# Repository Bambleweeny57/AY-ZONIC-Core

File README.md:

# 🔊AY-ZONIC-Core

AY-ZONIC-Core is a modular PSG interface designed for the ZX81, supporting both ZON-X and ZON-X-81 compatibility via simplified A4-only decode logic. Rev2.0 introduces gate economy, contributor-friendly schematic clarity, and expansion-ready I/O via AY-3-8912 Port A.

> **This project continues from [JonZON-X](https://github.com/Bambleweeny57/JonZON-X), which was closed at Rev1.4** after timing issues were discovered in demo playback. AY-ZONIC-Core retains the same A4-based decode logic but drops A5 and A6 simplifying the design to single PSG support and saving a gate.

## 🔧 Features

- **Dual-mode decode logic** via DIP switch:
  - **DIP OFF** → A4 pulled high → ZON-X-81 mode
  - **DIP ON** → A4 sourced from ZX81 Expansion Bus → ZON-X mode
- **AY-3-8912 PSG integration** with clean register selection and audio output
- **Series resistors** on data bus for signal protection
- **Pull-ups** from ZX81 Expansion Bus to PSG for stable logic levels
- **Port A expansion header** with +5V and GND for SD card and I/O experimentation
- **/RD decode support** for future peripheral interaction and PSG reads
### DIP Switch Logic — A4 Routing Modes

| DIP Switch | A4 Source             | Mode         | Description                                      |
|------------|-----------------------|--------------|--------------------------------------------------|
| OFF        | Pulled high (via pull-up) | ZON-X-81     | Forces A4 = 1 for simplified decode              |
| ON         | From ZX81 Expansion Bus  | ZON-X        | Enables dynamic A4 control from host             |

> This DIP-controlled logic allows seamless switching between ZON-X and ZON-X-81 compatibility without modifying the schematic.
> 
## 🧠 Decode Logic Overview

The schematic uses simplified A4-only address decoding, inherited from JonZON-X Rev1.4. By removing A5 and A6 from the decode path, Rev2.0 drops multi-PSG support in favor of gate economy and contributor clarity.

## 🖼️ Visual Decode Logic

### Decode Logic Explanation

The PSG is selected when:
- **A4 = 1** (via DIP or bus)
- **A7 = 1** (to avoid bus conflicts)
- **A2 = 1** (used internally by the PSG)
- **/IOREQ = 0** (active I/O cycle)
- **/WR and /RD** combinations determine the operation:
  - `/WR = 1`, `/RD = 1` → Write to register
  - `/WR = 0`, `/RD = 1` → Write to PSG
  - `/WR = 0`, `/RD = 0` → Read from PSG

> `/RD` is now decoded explicitly to support read operations from the PSG and future SD card and I/O interfaces.

### Reference — JonZON-X Rev1.4 Decode Matrix (A5/A6 omitted) for AY-ZONIC-Core

| A0–A4 | A2 | A7 | /IOREQ | /WR | /RD | BDIR | BC1 | Operation             |
|-------|----|----|--------|-----|-----|------|-----|------------------------|
| —     | 1  | 1  | 0      | 1   | 1   | 1    | 1   | Write to register      |
| —     | 1  | 1  | 0      | 0   | 1   | 0    | 1   | Write to PSG           |
| —     | 1  | 1  | 1      | 0   | 0   | 1    | 0   | Read from PSG          |
| —     | —  | —  | —      | —   | —   | 0    | 0   | Inactive               |

> Rev2.0 removes A5 and A6, streamlining the logic and focusing on single PSG support.

---

## 🔌 Expansion Header (Port A)

Port A of the AY-3-8912 exposes:
- **8 digital I/O lines** (AIO0–AIO7)
- **+5V** and **GND** for powering peripherals

This enables SD card interfacing, experimental I/O modules, and future expansion without modifying the core schematic.

### 🧵 AY-ZONIC-Core I/O Connector Pinout

| Pin | Signal | Description            |
|-----|--------|------------------------|
| 1   | 5V     | Power supply (5 volts) |
| 2   | A0     | Address line 0         |
| 3   | A1     | Address line 1         |
| 4   | A2     | Address line 2         |
| 5   | A3     | Address line 3         |
| 6   | A4     | Address line 4         |
| 7   | A5     | Address line 5         |
| 8   | A6     | Address line 6         |
| 9   | A7     | Address line 7         |
| 10  | GND    | Ground                 |

> This header is ideal for SD card experiments, LED arrays, or future playback logic modules. All signals are directly mapped from the AY-3-8912 Port A.

---

## 🗂️ Repository Structure

- `README.md` — This file
- `src/` — schematic and PCB design files (KiCad v9+)
- `pdf/ay-zonic-core.pdf` — Rev2.x schematic (KiCad source available from /src)
- `images/` — Decode logic diagram and overlays
- `fabfiles/` — Gerber and Exelon Drill fabrication files
- `docs/` — Contributor notes and onboarding diagrams (coming soon)

## 🧭 Contributor Notes

- Keep DIP switch logic annotated in overlays
- Label Port A lines clearly for expansion use
- Use series resistors and pull-ups as shown for safe bus interaction
- Future revisions may include playback logic or UI hooks — modularity is key

## 🛠️ Status

✅ Rev2.0 schematic complete  
🧪 Expansion header tested with SD interface  
📚 Documentation in progress

---

For questions, forks, or onboarding help, feel free to open an issue or start a discussion. Let the AY-3-8912 sing!

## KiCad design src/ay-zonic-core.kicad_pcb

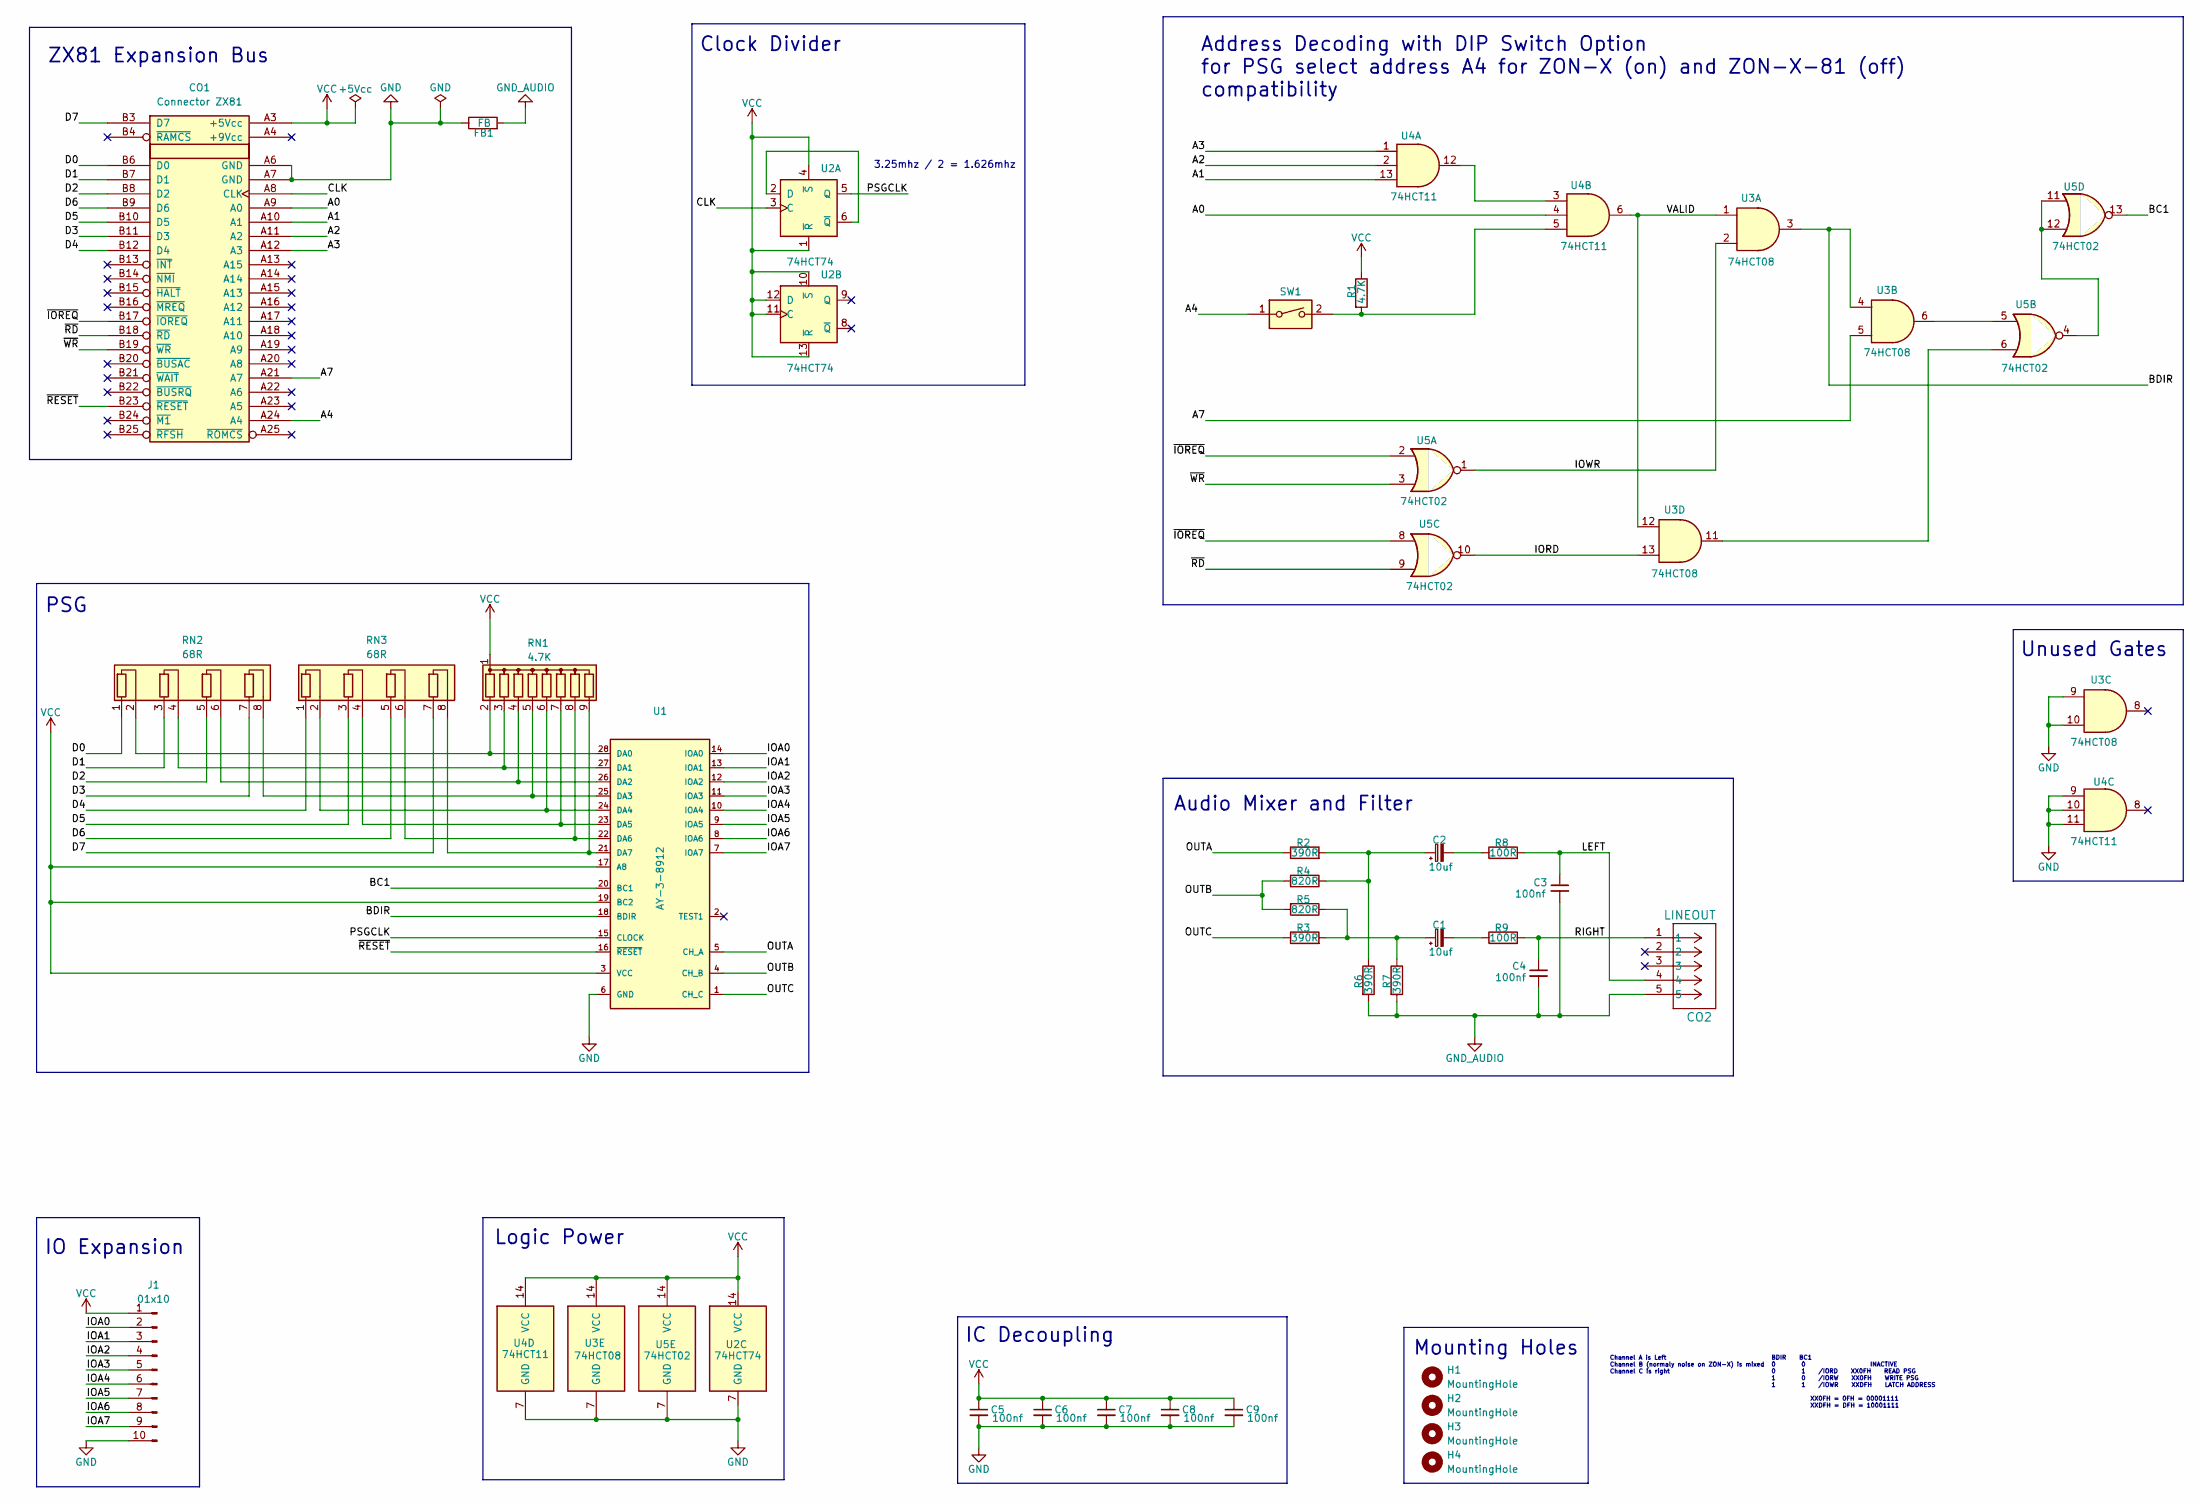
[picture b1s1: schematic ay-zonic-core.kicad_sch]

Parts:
C1, C2: 10uf; CP_Radial_D5.0mm_P2.00mm
C3, C4, C5, C6, C7, C8, C9: 100nf; C_Disc_D3.0mm_W1.6mm_P2.50mm
CO1: Connector ZX81; ZX81_EdgeConnector
CO2: LINEOUT; CONN5_SPC21348_MTC
FB1: FB; R_Axial_DIN0207_L6.3mm_D2.5mm_P7.62mm_Horizontal
H1, H2, H3, H4: MountingHole; MountingHole_3.2mm_M3_DIN965_Pad
J1: 01x10; PinHeader_1x10_P2.54mm_Vertical
R1: 4.7K; R_Axial_DIN0207_L6.3mm_D2.5mm_P7.62mm_Horizontal
R2, R3, R6, R7: 390R; R_Axial_DIN0207_L6.3mm_D2.5mm_P7.62mm_Horizontal
R4, R5: 820R; R_Axial_DIN0207_L6.3mm_D2.5mm_P7.62mm_Horizontal
R8, R9: 100R; R_Axial_DIN0207_L6.3mm_D2.5mm_P7.62mm_Horizontal
RN1: 4.7K; R_Array_SIP9
RN2, RN3: 68R; R_Array_SIP8
SW1: SW_DIP_x01; SW_DIP_SPSTx01_Slide_9.78x4.72mm_W7.62mm_P2.54mm
U1: AY-3-8912; DIP-28_W15.24mm_LongPads
U2: 74HCT74; DIP-14_W7.62mm_LongPads
U3: 74HCT08; DIP-14_W7.62mm_LongPads
U4: 74HCT11; DIP-14_W7.62mm_LongPads
U5: 74HCT02; DIP-14_W7.62mm_LongPads

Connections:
/A0: CO1.A9 (A0), U4.4
/A1: CO1.A10 (A1), U4.13
/A2: CO1.A11 (A2), U4.2
/A3: CO1.A12 (A3), U4.1
/A4: CO1.A24 (A4), SW1.1
/A7: CO1.A21 (A7), U3.5
/BC1: U1.20 (BC1), U5.13
/BDIR: U1.18 (BDIR), U3.3, U3.4
/CLK: CO1.A8 (CLK), U2.3 (C)
/D0: CO1.B6 (D0), RN2.1 (R1.1)
/D1: CO1.B7 (D1), RN2.3 (R2.1)
/D2: CO1.B8 (D2), RN2.5 (R3.1)
/D3: CO1.B11 (D3), RN2.7 (R4.1)
/D4: CO1.B12 (D4), RN3.1 (R1.1)
/D5: CO1.B10 (D5), RN3.3 (R2.1)
/D6: CO1.B9 (D6), RN3.5 (R3.1)
/D7: CO1.B3 (D7), RN3.7 (R4.1)
/IOA0: J1.2, U1.14 (IOA0); also elsewhere on the board
/IOA1: J1.3, U1.13 (IOA1); also elsewhere on the board
/IOA2: J1.4, U1.12 (IOA2); also elsewhere on the board
/IOA3: J1.5, U1.11 (IOA3); also elsewhere on the board
/IOA4: J1.6, U1.10 (IOA4); also elsewhere on the board
/IOA5: J1.7, U1.9 (IOA5); also elsewhere on the board
/IOA6: J1.8, U1.8 (IOA6); also elsewhere on the board
/IOA7: J1.9, U1.7 (IOA7); also elsewhere on the board
/IORD: U3.13, U5.10
/IOWR: U3.2, U5.1
/LEFT: C3.1, CO2.4, R8.2; also elsewhere on the board
/OUTA: R2.1, U1.5 (CH_A)
/OUTB: R4.2, R5.2, U1.4 (CH_B)
/OUTC: R3.1, U1.1 (CH_C)
/PSGCLK: U1.15 (CLOCK), U2.5 (Q)
/RIGHT: C4.1, CO2.1, R9.2; also elsewhere on the board
/VALID: U3.1, U3.12, U4.6
/~IOREQ: CO1.B17 (~IOREQ), U5.2, U5.8
/~RD: CO1.B18 (~RD), U5.9
/~RESET: CO1.B23 (~RESET), U1.16 (~RESET)
/~WR: CO1.B19 (~WR), U5.3
GND: C5.2, C6.2, C7.2, C8.2, C9.2, CO1.A6 (GND), CO1.A7 (GND), FB1.1, J1.10, U1.6 (GND), U2.7 (GND), U3.7 (GND), U3.9, U3.10, U4.7 (GND), U4.9, U4.10, U4.11, U5.7 (GND); also elsewhere on the board
GND_AUDIO: C3.2, C4.2, CO2.5, FB1.2, R6.2, R7.2; also elsewhere on the board
unnamed: C1.1, R3.2, R5.1, R7.1
unnamed: C1.2, R9.1
unnamed: C2.1, R2.2, R4.1, R6.1
unnamed: C2.2, R8.1
unnamed: R1.2, SW1.2, U4.5
unnamed: RN1.2 (R1), RN2.2 (R1.2), U1.28 (DA0)
unnamed: RN1.3 (R2), RN2.4 (R2.2), U1.27 (DA1)
unnamed: RN1.4 (R3), RN2.6 (R3.2), U1.26 (DA2)
unnamed: RN1.5 (R4), RN2.8 (R4.2), U1.25 (DA3)
unnamed: RN1.6 (R5), RN3.2 (R1.2), U1.24 (DA4)
unnamed: RN1.7 (R6), RN3.4 (R2.2), U1.23 (DA5)
unnamed: RN1.8 (R7), RN3.6 (R3.2), U1.22 (DA6)
unnamed: RN1.9 (R8), RN3.8 (R4.2), U1.21 (DA7)
unnamed: U2.2 (D), U2.6 (~Q)
unnamed: U3.6, U5.5
unnamed: U3.11, U5.6
unnamed: U4.3, U4.12
unnamed: U5.4, U5.11, U5.12
VCC: C5.1, C6.1, C7.1, C8.1, C9.1, CO1.A3 (+5Vcc), J1.1, R1.1, RN1.1 (common), U1.3 (VCC), U1.17 (A8), U1.19 (BC2), U2.1 (~R), U2.4 (~S), U2.10 (~S), U2.11 (C), U2.12 (D), U2.13 (~R), U2.14 (VCC), U3.14 (VCC), U4.14 (VCC), U5.14 (VCC); also elsewhere on the board

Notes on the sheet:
IO Expansion
Audio Mixer and Filter
ZX81 Expansion Bus
3.25mhz / 2 = 1.626mhz
Unused Gates
Address Decoding with DIP Switch Option for PSG select address A4 for ZON-X (on) and ZON-X-81 (off) compatibility
IC Decoupling
Mounting Holes
Logic Power
Channel A is Left Channel B (normaly noise on ZON-X) is mixed Channel C is right
PSG
BDIR BC1 0 0 INACTIVE 0 1 /IORD XX0FH READ PSG 1 0 /IORW XX0FH WRITE PSG 1 1 /IOWR XXDFH LATCH ADDRESS XX0FH = 0FH = 00001111 XXDFH = DFH = 10001111
Clock Divider

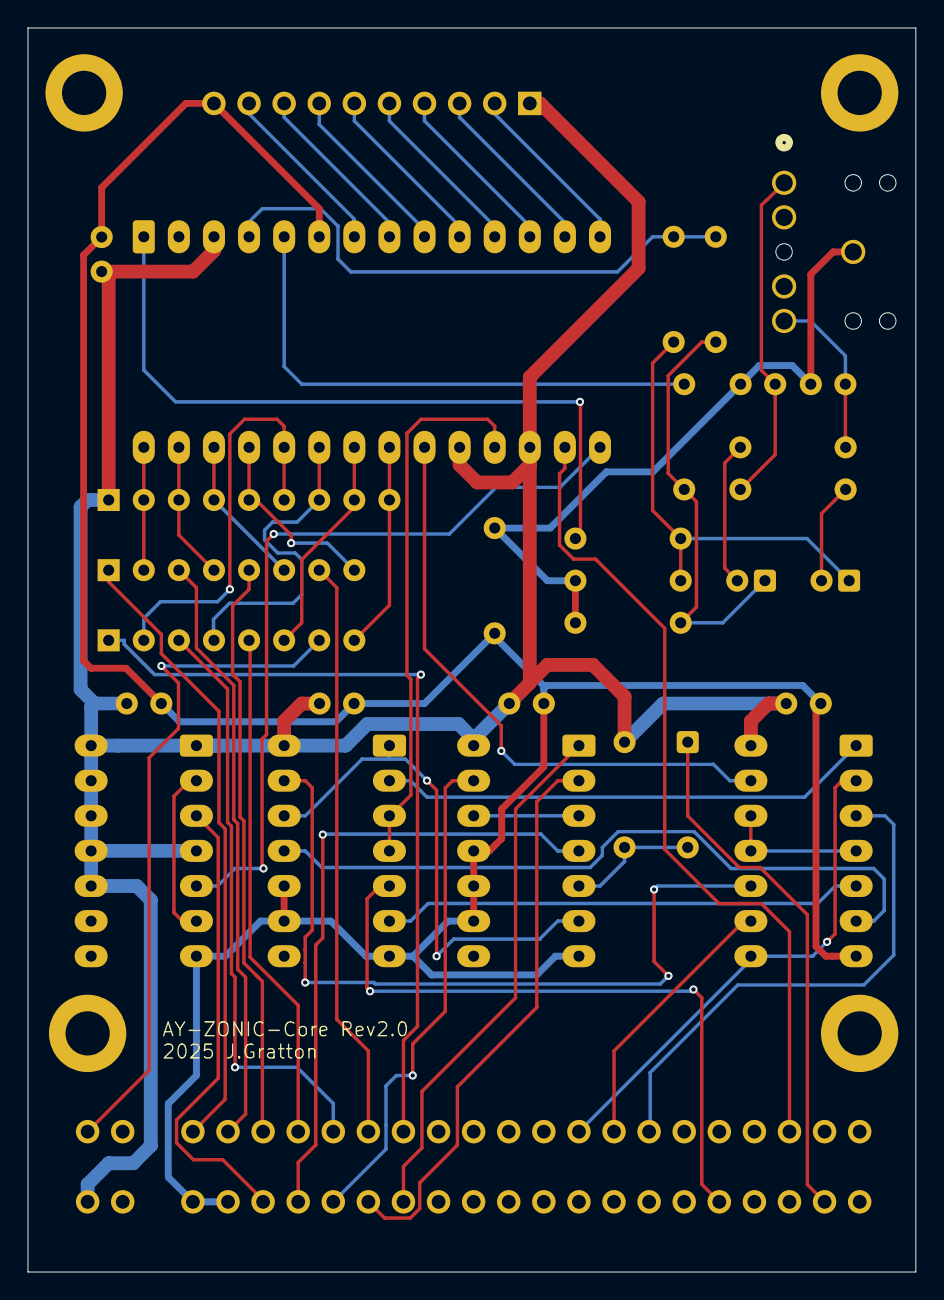
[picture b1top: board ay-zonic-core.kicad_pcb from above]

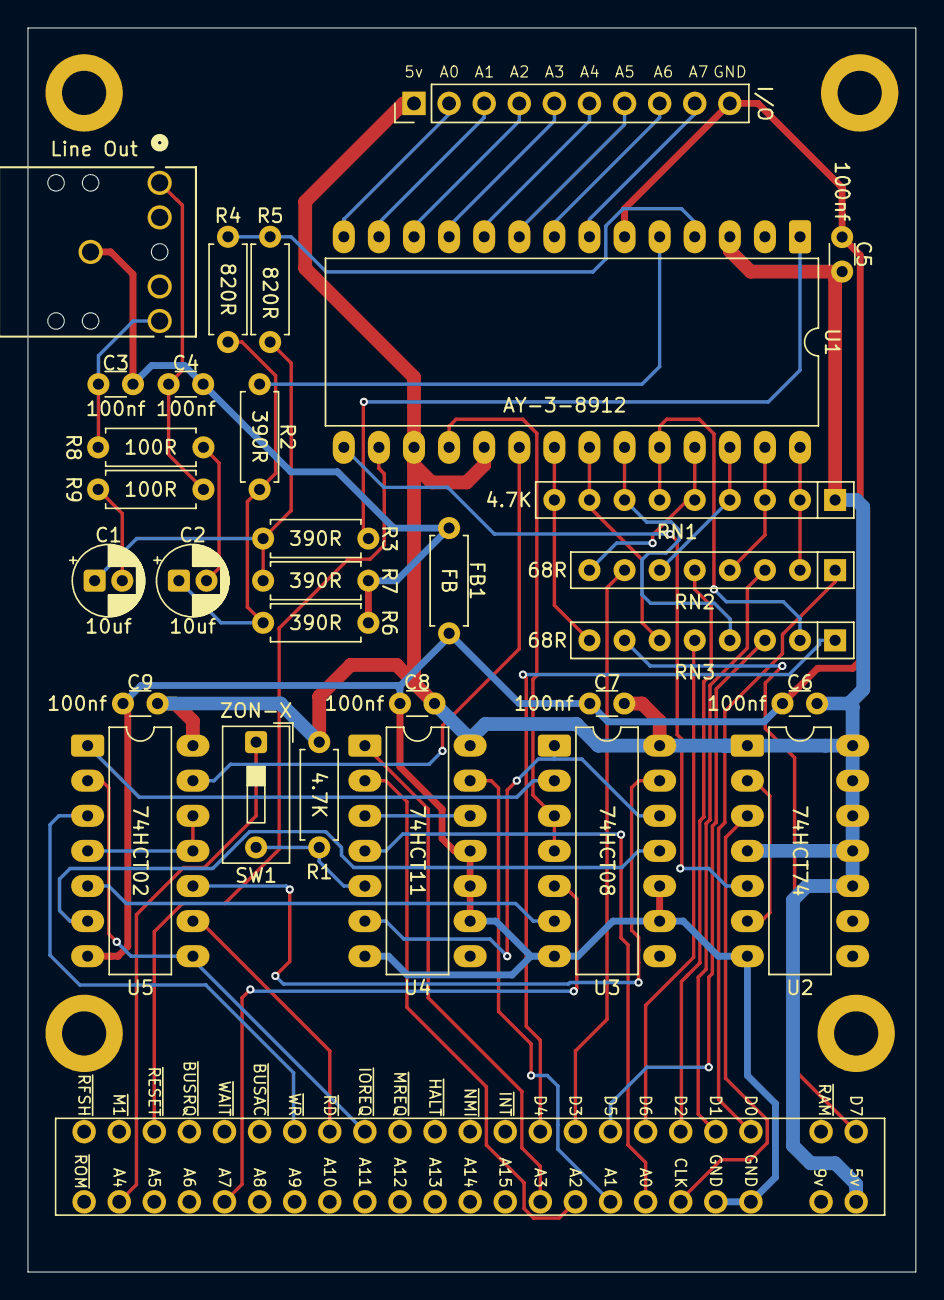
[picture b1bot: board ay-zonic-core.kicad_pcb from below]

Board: 2 copper layers, 64.3 x 90.0 mm, 35 parts (30 on the bottom side), 59 nets.

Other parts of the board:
I/O: 01x10; PinHeader_1x10_P2.54mm_Vertical
Line Out: LINEOUT; CONN5_SPC21348_MTC

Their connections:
/IOA0: I/O.2; also elsewhere on the board
/IOA1: I/O.3; also elsewhere on the board
/IOA2: I/O.4; also elsewhere on the board
/IOA3: I/O.5; also elsewhere on the board
/IOA4: I/O.6; also elsewhere on the board
/IOA5: I/O.7; also elsewhere on the board
/IOA6: I/O.8; also elsewhere on the board
/IOA7: I/O.9; also elsewhere on the board
/LEFT: Line Out.4; also elsewhere on the board
/RIGHT: Line Out.1; also elsewhere on the board
GND: I/O.10; also elsewhere on the board
GND_AUDIO: Line Out.5; also elsewhere on the board
VCC: I/O.1; also elsewhere on the board

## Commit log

2025-09-20 Initial push
2025-09-20 added image of decode logic
2025-09-21 Added schematic symbols and footprints
2025-09-24 added 3d model for edge connector and footprints plus added schematic to pcb.
2025-09-24 new back 3D image
2025-09-24 new pdf of the schematic
2025-09-25 added labels to IO connector
2025-09-25 updated readme with IO header
2025-09-25 routed and new images
2025-09-25 added iBOM
2025-09-25 Added fab files
2025-09-25 saved pcb
2025-09-28 added mounting holes and started routing.
2025-09-28 updated routing
2025-09-29 final route rev 2.0
2025-09-29 updated readme for fab files
2025-09-30 rerouted a few things to make them better
